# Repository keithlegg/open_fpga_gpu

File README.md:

# open_fpga_gpu

HERE THERE BE DRAGONS.

This is an experiment. This is probably never going to be much more than that. 

It currently works as an SRAM framebuffer, it can draw the contents of memory to VGA and only draws a single line on the screen.

There will be much done to it before it is even close to ready to be called a "GPU".

HARDWARE:

Features 2 IS62WV51216BLL SRAM chips.

Each SRAM chip has 512K x 16 CMOS low power static RAM

Both chips share the address and data bus with separate programable control lines.

Also has a slot for a 1bitsy ARM chip, not wired directly to the FPGA but there are headers if you want to.

Every mojo pin has been broken out so you can snoop with logic tools, or reconfigure how you want. 
This makes the board much larger, but keeps things easier for prototyping. 

The verilog is added to the mojo-base-project found here:

    https://github.com/embmicro/mojo-base-project

Just copy the files into the src folder, and add the link in ISE GUI before you build the project.

Bresenham code borrowed from here:

    https://github.com/kavinr/Bresenham-Line-Drawing-Algorithm

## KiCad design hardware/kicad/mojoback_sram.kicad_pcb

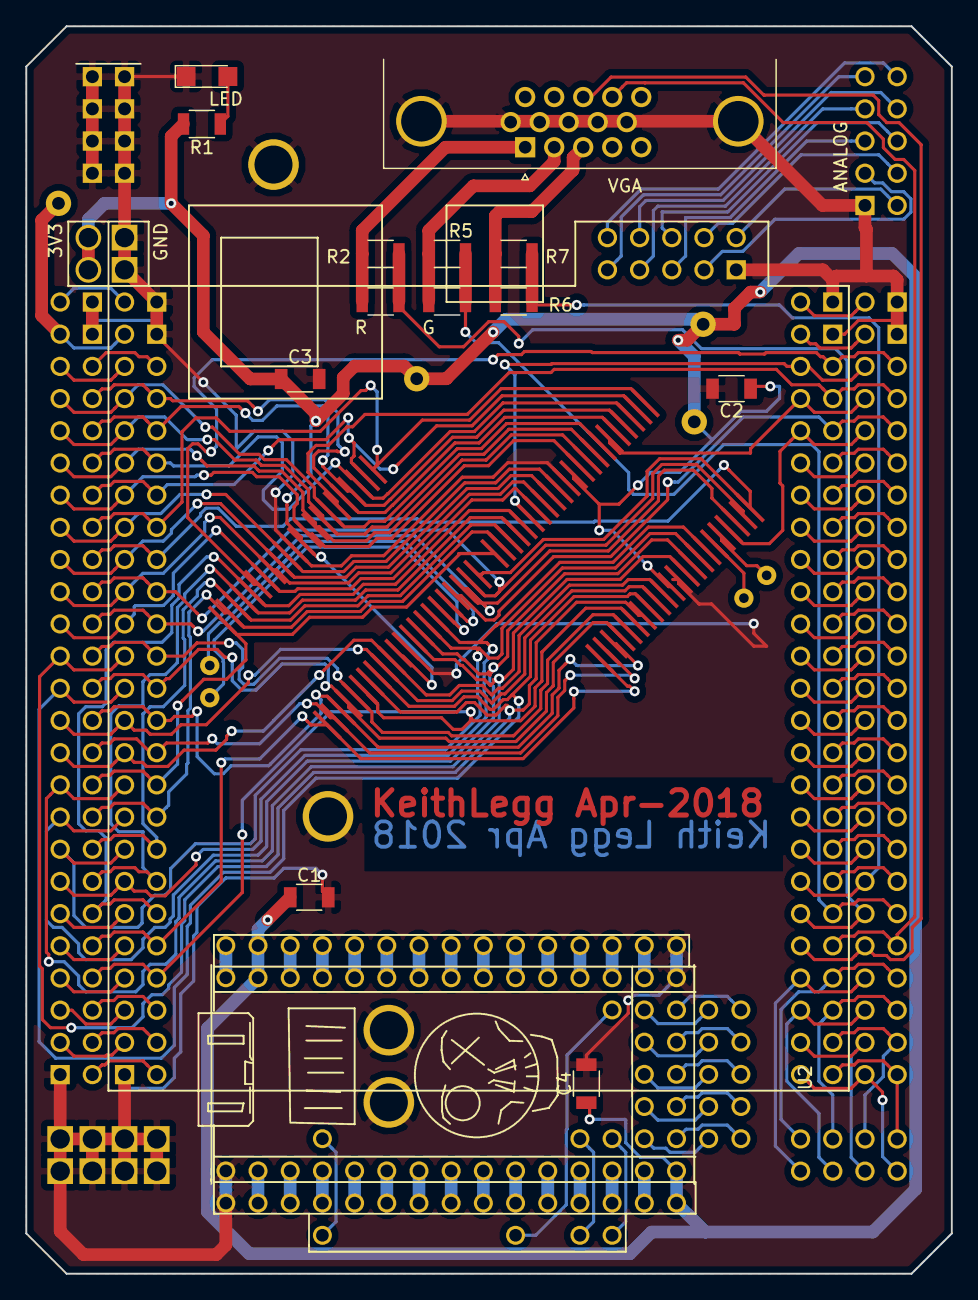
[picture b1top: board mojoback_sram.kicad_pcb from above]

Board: 2 copper layers, 73.0 x 98.4 mm, 16 parts (0 on the bottom side), 44 nets.

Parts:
C1, C2, C3, C4: .1uf; C_1206
G: G; R_1206
LED: LED; LED_1206
R, R1: R; R_1206
R2, R5, R7: R_1206
R6: B; R_1206
SRAM1, SRAM2: 62WV51212ALL; KL_TSOP44_Pitch0.8mm
U2: kl_bitsy
VGA: kl_VGA; KL_VGA

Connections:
/3V3: C1.1, C2.1, C3.1, C4.1, R1.2, SRAM1.11, SRAM1.33, SRAM2.11, SRAM2.33, U2.18, U2.42
/A0: SRAM1.5, SRAM2.5
/A1: SRAM1.4, SRAM2.4
/A2: SRAM1.3, SRAM2.3
/A3: SRAM1.2, SRAM2.2
/A4: SRAM1.1, SRAM2.1
/A5: SRAM1.44, SRAM2.44
/A6: SRAM1.43, SRAM2.43
/A7: SRAM1.42, SRAM2.42
/A8: SRAM1.27, SRAM2.27
/A9: SRAM1.26, SRAM2.26
/A10: SRAM1.25, SRAM2.25
/A11: SRAM1.24, SRAM2.24
/A12: SRAM1.22, SRAM2.22
/A13: SRAM1.21, SRAM2.21
/A14: SRAM1.20, SRAM2.20
/A15: SRAM1.19, SRAM2.19
/A16: SRAM1.18, SRAM2.18
/A17: SRAM1.23, SRAM2.23
/A18: SRAM1.28, SRAM2.28
/IO_0: SRAM1.7, SRAM2.7
/IO_1: SRAM1.8, SRAM2.8
/IO_2: SRAM1.9, SRAM2.9
/IO_3: SRAM1.10, SRAM2.10
/IO_4: SRAM1.13, SRAM2.13
/IO_5: SRAM1.14, SRAM2.14
/IO_6: SRAM1.15, SRAM2.15
/IO_7: SRAM1.16, SRAM2.16
/IO_8: SRAM1.29, SRAM2.29
/IO_9: SRAM1.30, SRAM2.30
/IO_10: SRAM1.31, SRAM2.31
/IO_11: SRAM1.32, SRAM2.32
/IO_12: SRAM1.35, SRAM2.35
/IO_13: SRAM1.36, SRAM2.36
/IO_14: SRAM1.37, SRAM2.37
/IO_15: SRAM1.38, SRAM2.38
/b_video: R6.2, R7.2
/clr_b: R6.1, R7.1, VGA.3
/clr_g: G.1, R5.1, VGA.2
/clr_r: R.1, R2.1, VGA.1
/g_video: G.2, R5.2
/r_video: R.2, R2.2
GND: C1.2, C2.2, C3.2, C4.2, LED.1, SRAM1.12, SRAM1.34, SRAM2.12, SRAM2.34, U2.1, U2.29, VGA.0
unnamed: LED.2, R1.1

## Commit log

2018-12-25 first
2018-12-25 second
2018-12-25 images
2018-12-25 images 2
2018-12-25 added verilog files
2018-12-25 more verilog
2018-12-25 edit readme
2018-12-25 readme
2024-11-19 who cares?
